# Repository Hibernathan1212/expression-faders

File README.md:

# Expression Faders

A simple midi controller with 2 faders and 2 rotary encoders. This was made for adding midi cc1 and cc11 while playing midi instruments such as strings to give more dynamic range and expression. The rotary encoders can also be mapped to any track specific features such as volume or other daw macros.

The goal was to be able to add more dynamic control while playing on a midi keyboard. Inspired by [Christian Henson](https://youtu.be/O5ax1lMdYO0?si=J35fgkykRBnHvoFT&t=346) and his approach to string writing and playing on a midi keyboard.

## Features

- 2 ptb0143 100mm faders for controlling midi cc
- 2 ec11 rotary encoders for controlling other daw values such as volume
- Xiao rp2040 for its midi support and size
- Has multiple decoupling caps to ground to reduce electronic noise from signal

## CAD

Consists of a base and a top lid that slots in a lip on the base. PCB is mounted to the lid with 4 m3 screws that go into the faders.

Made in Onshape.

[source](https://cad.onshape.com/documents/7d573544174621b2e2808d4e/w/58510c4aadba22e801dceb47/e/146ecd20f6130f1f9171a54c?renderMode=0&uiState=69f439aeeff61854c6391ffe)

## PCB

Made in Kicad.

### Schematic

### PCB

## Firmware

Uses python with the usb midi library and adafruit to take the GPIO input and send midi signals back to the computer. Has a hysteresis threshold to try and reduce electronic noise.

## BOM

| Product                   | Amount | Unit Cost (THB) | Price (THB) | Price (USD) | Link                                                                                                                                                                                                                                                                                         |
| ------------------------- | ------ | --------------- | ----------- | ----------- | -------------------------------------------------------------------------------------------------------------------------------------------------------------------------------------------------------------------------------------------------------------------------------------------- |
| EC11                      | 2      | 81.42           | 162.84      | 5.00        | [https://th.element14.com/alps/ec11k1524402/encoder-vertical-11mm-30det-15ppr/dp/2064998](https://th.element14.com/alps/ec11k1524402/encoder-vertical-11mm-30det-15ppr/dp/2064998)                                                                                                           |
| ptb0143                   | 2      | 178.46          | 356.92      | 10.97       | [https://th.element14.com/bourns/ptb0143-2010bpb103/potentiometer-slide-10k-100mm/dp/1688409](https://th.element14.com/bourns/ptb0143-2010bpb103/potentiometer-slide-10k-100mm/dp/1688409)                                                                                                   |
| orpheus pico              | 1      | ?               | ?           | 0.00        |                                                                                                                                                                                                                                                                                              |
| m3 screws                 | 4      |                 | 132         | 4.06        | [https://th.element14.com/tr-fastenings/m35-bh10mcs100/screw-socket-butt-m3x5-pk100/dp/1420682](https://th.element14.com/tr-fastenings/m35-bh10mcs100/screw-socket-butt-m3x5-pk100/dp/1420682)                                                                                               |
| 100nf 0805 smd capacitors | 10     | 0.43            | 4.3         | 0.13        | [https://th.element14.com/multicomp-pro/mc0805b104k250ct/cap-0-1-f-25v-10-x7r-0805/dp/1759166](https://th.element14.com/multicomp-pro/mc0805b104k250ct/cap-0-1-f-25v-10-x7r-0805/dp/1759166) |
| element 14 shipping       |        |                 | 550         | 16.90       |                                                                                                                                                                                                                                                                                              |
| jlcpcb                    |        |                 |             | 12.13       |                                                                                                                                                                                                                                                                                              |
|                           |        |                 |             |             |                                                                                                                                                                                                                                                                                              |
| total                     |        |                 |             | 49.18       |                                                                                                                                                                                                                                                                                              |

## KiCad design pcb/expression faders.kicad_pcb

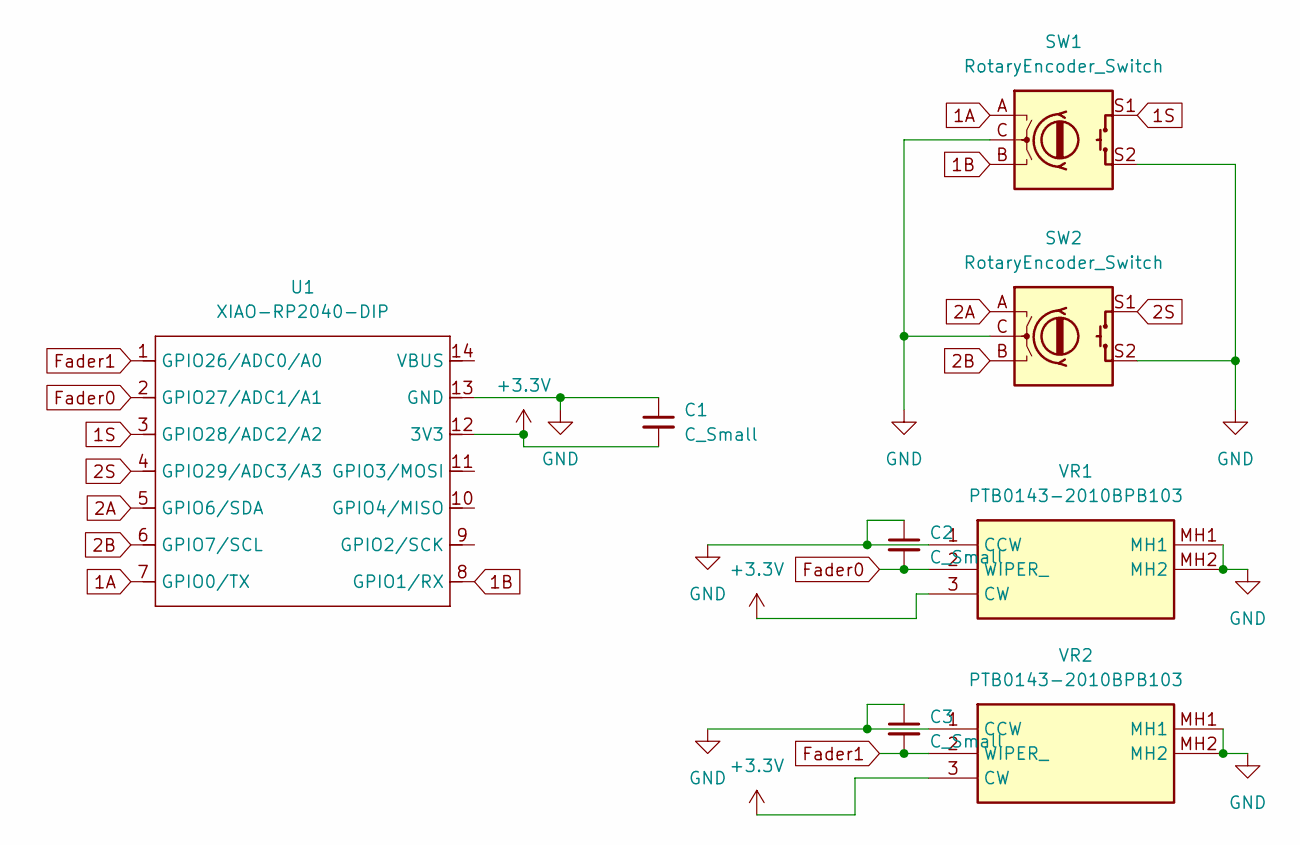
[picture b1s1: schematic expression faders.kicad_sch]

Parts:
C1, C2, C3: C_Small; C_0805_2012Metric
SW1, SW2: RotaryEncoder_Switch; RotaryEncoder_Alps_EC11E-Switch_Vertical_H20mm
U1: XIAO-RP2040-DIP; XIAO-Generic-Hybrid-14P-2.54-21X17.8MM
VR1, VR2: PTB0143-2010BPB103; PTB01432010BPB103; Manufacturer_Part_Number PTB0143-2010BPB103; Mouser Part Number 652-PTB1432010BPB103

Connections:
1A: SW1.A, U1.7 (GPIO0/TX)
1B: SW1.B, U1.8 (GPIO1/RX)
1S: SW1.S1, U1.3 (GPIO28/ADC2/A2)
2A: SW2.A, U1.5 (GPIO6/SDA)
2B: SW2.B, U1.6 (GPIO7/SCL)
2S: SW2.S1, U1.4 (GPIO29/ADC3/A3)
+3.3V: C1.2, U1.12 (3V3), VR1.3 (CW), VR2.3 (CW)
Fader0: C2.2, U1.2 (GPIO27/ADC1/A1), VR1.2 (WIPER_)
Fader1: C3.2, U1.1 (GPIO26/ADC0/A0), VR2.2 (WIPER_)
GND: C1.1, C2.1, C3.1, SW1.C, SW1.S2, SW2.C, SW2.S2, U1.13 (GND), VR1.1 (CCW), VR1.MH1, VR1.MH2, VR2.1 (CCW), VR2.MH1, VR2.MH2

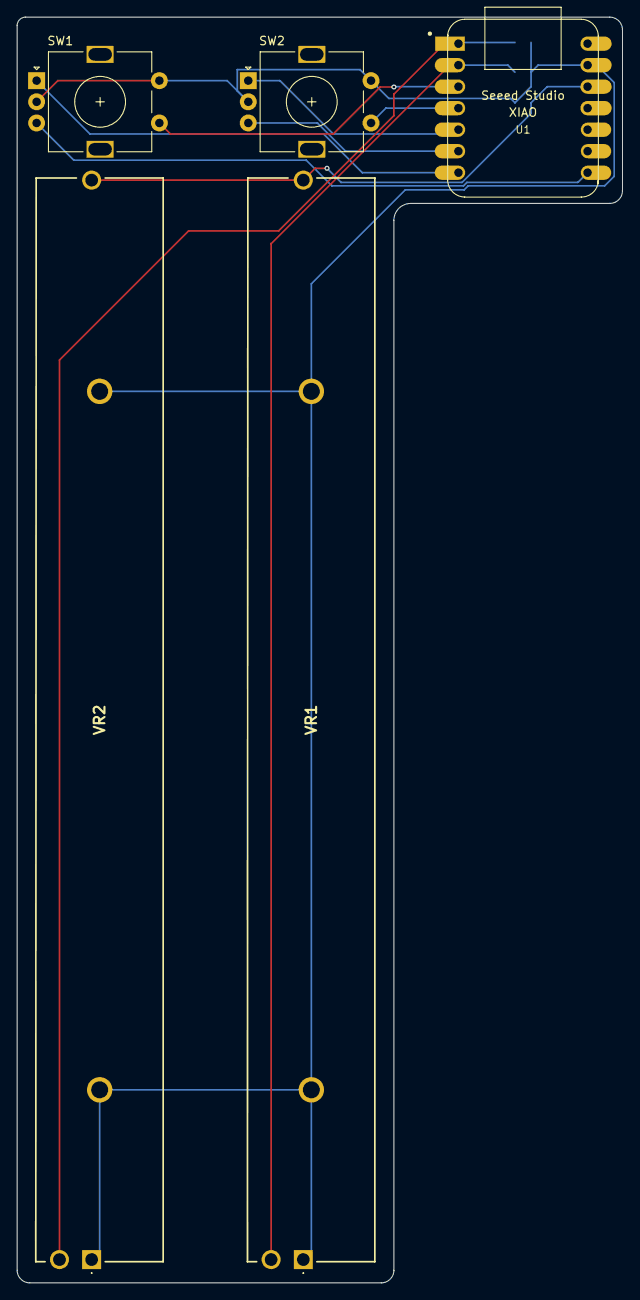
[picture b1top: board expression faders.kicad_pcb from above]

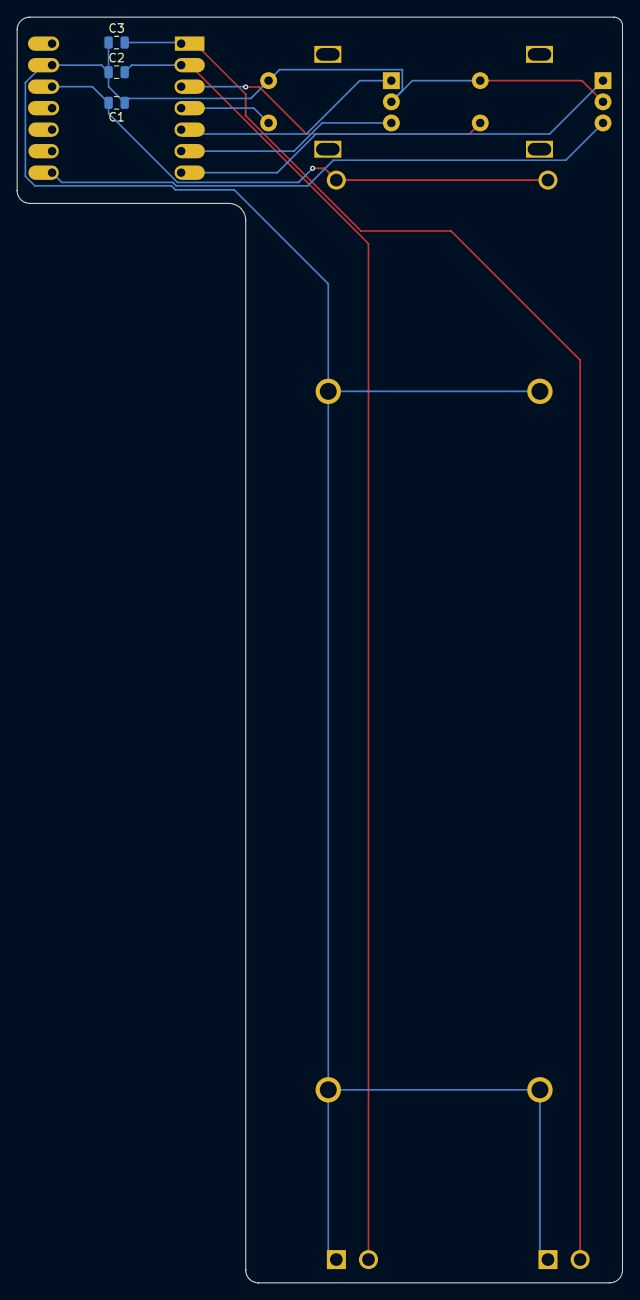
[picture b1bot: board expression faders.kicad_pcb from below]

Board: 2 copper layers, 71.5 x 149.5 mm, 8 parts (3 on the bottom side), 10 nets.

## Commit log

2026-04-01 init commit
2026-04-01 add readme
